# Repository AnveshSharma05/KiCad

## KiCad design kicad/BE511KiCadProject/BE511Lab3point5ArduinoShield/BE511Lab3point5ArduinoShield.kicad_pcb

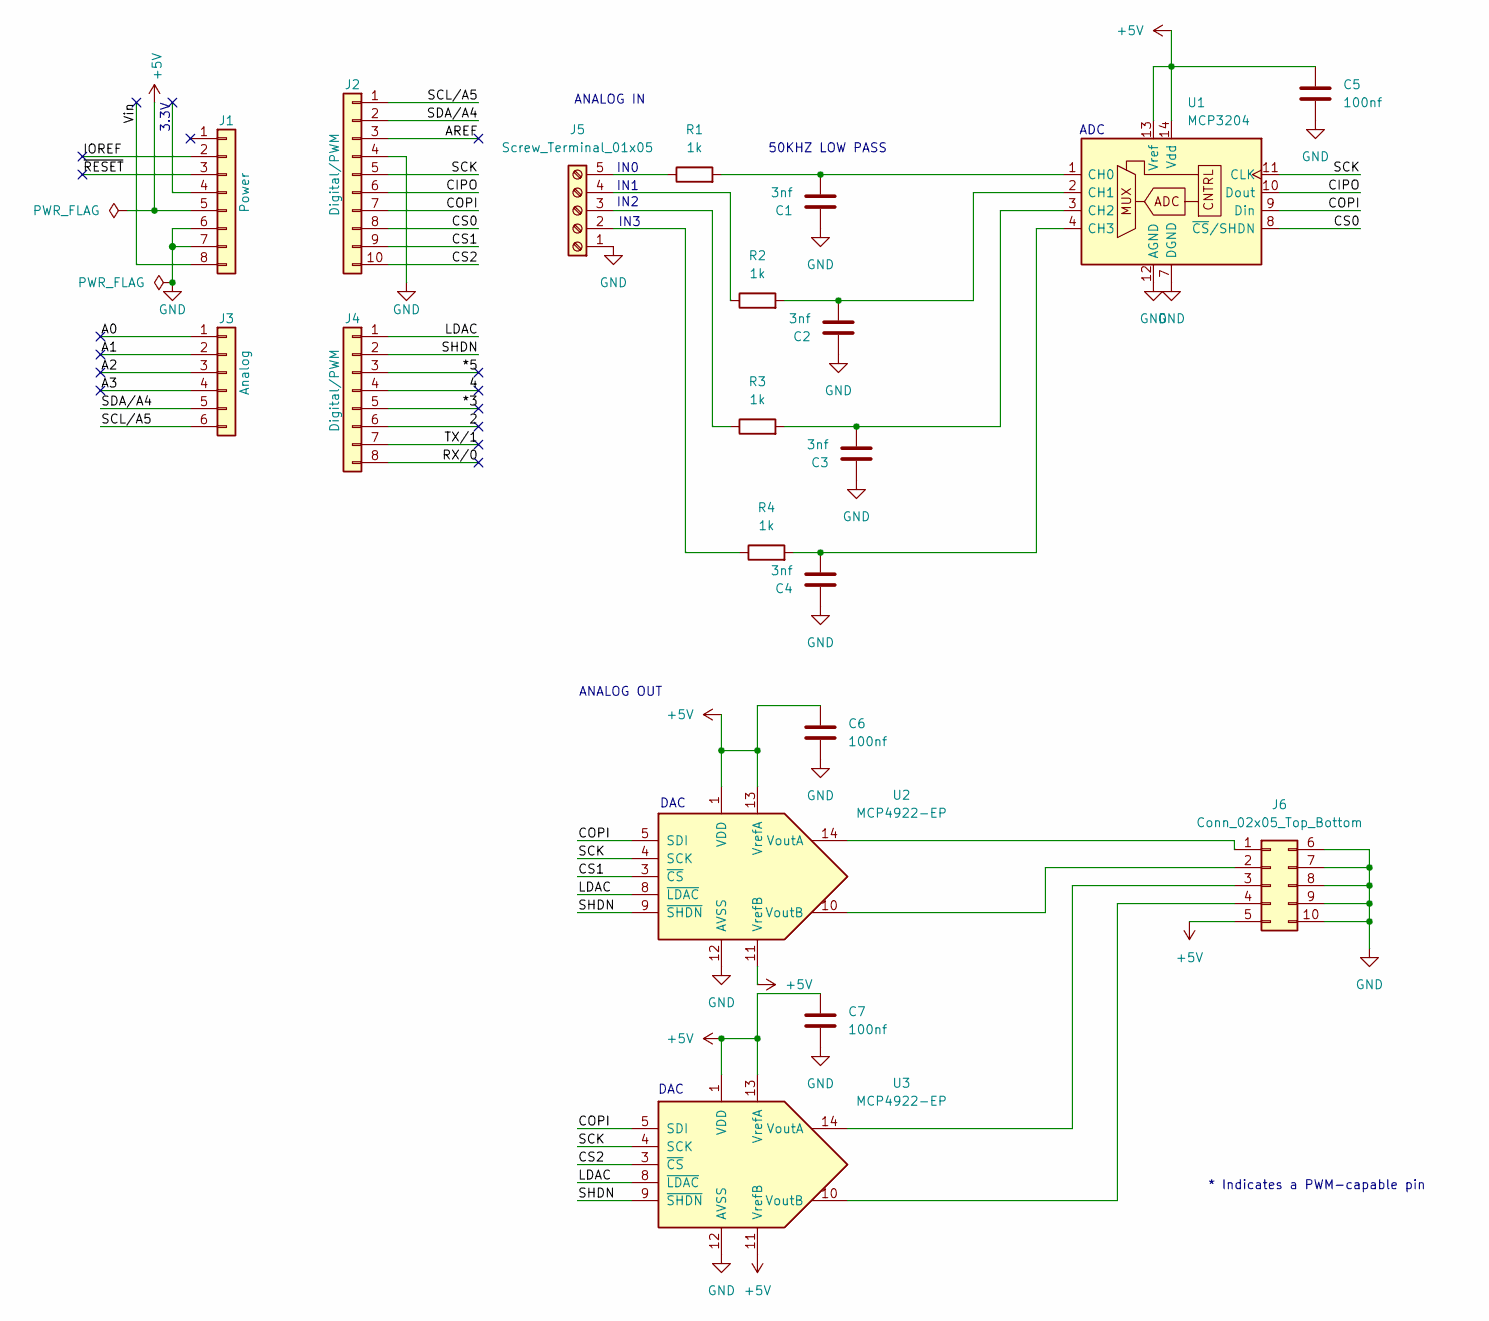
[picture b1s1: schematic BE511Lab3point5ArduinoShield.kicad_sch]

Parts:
C1, C2, C3, C4: 3nf
C5, C6, C7: 100nf
J1: Power; PinSocket_1x08_P2.54mm_Vertical
J2: Digital/PWM; PinSocket_1x10_P2.54mm_Vertical
J3: Analog; PinSocket_1x06_P2.54mm_Vertical
J4: Digital/PWM; PinSocket_1x08_P2.54mm_Vertical
J5: Screw_Terminal_01x05; TerminalBlock_Phoenix_MPT-0,5-5-2.54_1x05_P2.54mm_Horizontal
J6: Conn_02x05_Top_Bottom; PinHeader_2x05_P2.54mm_Vertical
R1, R2, R3, R4: 1k
U1: MCP3204; DIP-14_W7.62mm
U2, U3: MCP4922-EP; DIP-14_W7.62mm

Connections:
+5V: C5.2, C6.2, C7.2, J1.5, J6.5, U1.13 (Vref), U1.14 (Vdd), U2.1 (VDD), U2.11 (VrefB), U2.13 (VrefA), U3.1 (VDD), U3.11 (VrefB), U3.13 (VrefA)
/2: J4.6
/4: J4.4
/*3: J4.5
/*5: J4.3
/A0: J3.1
/A1: J3.2
/A2: J3.3
/A3: J3.4
/AREF: J2.3
/CIPO: J2.6, U1.10 (Dout)
/COPI: J2.7, U1.9 (Din), U2.5 (SDI), U3.5 (SDI)
/CS0: J2.8, U1.8 (~CS/SHDN)
/CS1: J2.9, U2.3 (~CS)
/CS2: J2.10, U3.3 (~CS)
/IOREF: J1.2
/LDAC: J4.1, U2.8 (~LDAC), U3.8 (~LDAC)
/RX/0: J4.8
/SCK: J2.5, U1.11 (CLK), U2.4 (SCK), U3.4 (SCK)
/SCL/A5: J2.1, J3.6
/SDA/A4: J2.2, J3.5
/SHDN: J4.2, U2.9 (~SHDN), U3.9 (~SHDN)
/TX/1: J4.7
/Vin: J1.8
/~RESET: J1.3
GND: C1.1, C2.1, C3.1, C4.1, C5.1, C6.1, C7.1, J1.6, J1.7, J2.4, J5.1, J6.6, J6.7, J6.8, J6.9, J6.10, U1.7 (DGND), U1.12 (AGND), U2.12 (AVSS), U3.12 (AVSS)
unnamed: J5.2, R4.1
unnamed: J5.3, R3.1
unnamed: J5.4, R2.1
unnamed: J5.5, R1.1
unnamed: J6.1, U2.14 (VoutA)
unnamed: J6.2, U2.10 (VoutB)
unnamed: J6.3, U3.14 (VoutA)
unnamed: J6.4, U3.10 (VoutB)
unnamed: C1.2, R1.2, U1.1 (CH0)
unnamed: C2.2, R2.2, U1.2 (CH1)
unnamed: C3.2, R3.2, U1.3 (CH2)
unnamed: C4.2, R4.2, U1.4 (CH3)

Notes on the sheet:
ANALOG IN
DAC
IN2
3.3V
50KHZ LOW PASS
ADC
IN3
IN1
ANALOG OUT
IN0
* Indicates a PWM-capable pin

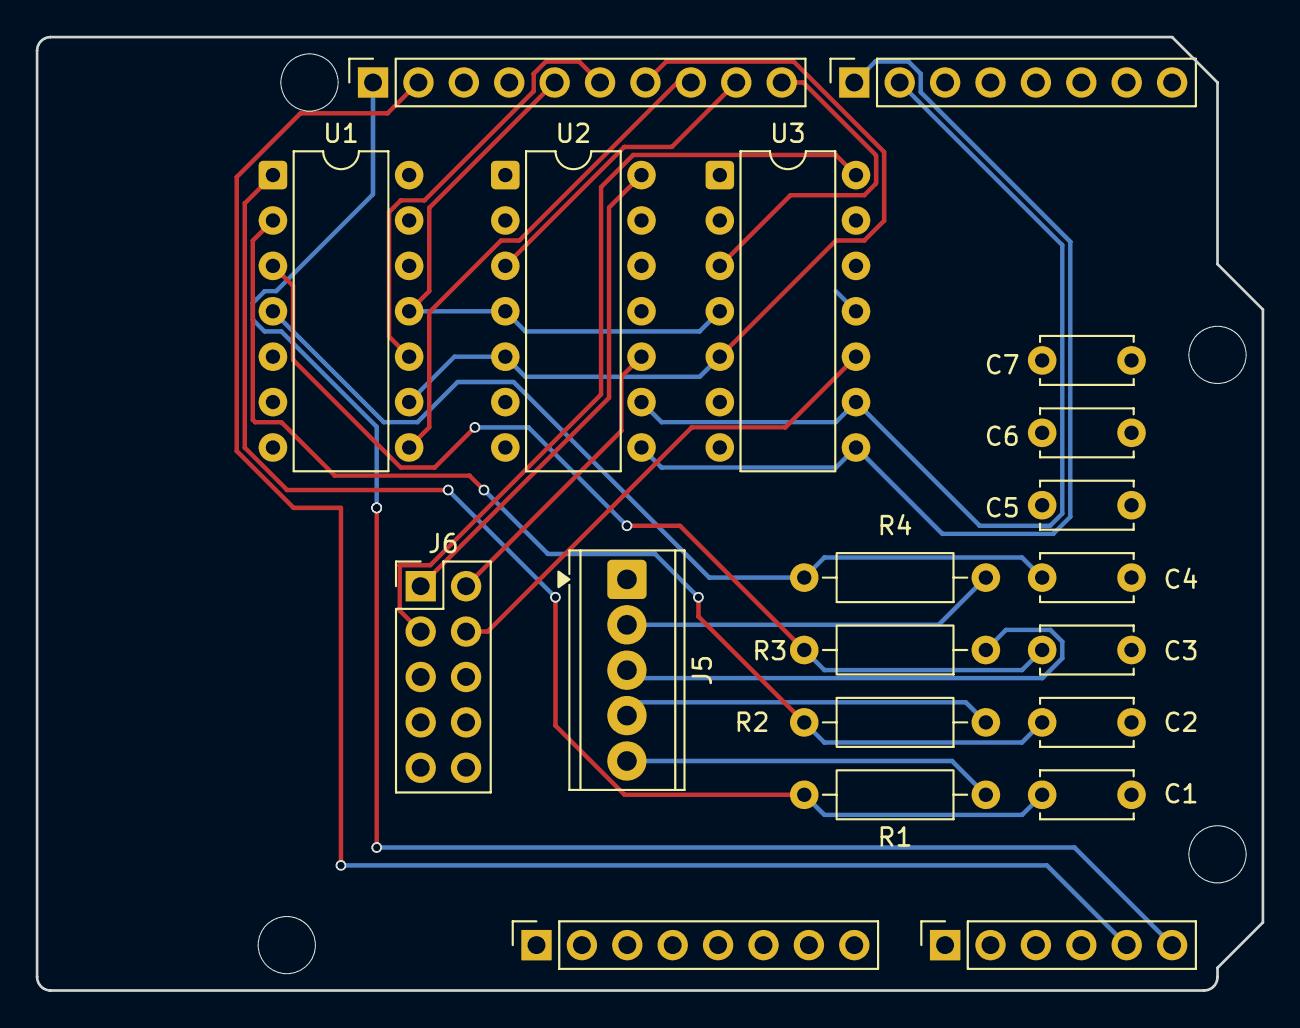
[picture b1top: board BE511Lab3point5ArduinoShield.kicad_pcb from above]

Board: 4 copper layers, 68.6 x 53.3 mm, 24 parts (0 on the bottom side), 24 nets.

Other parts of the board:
MH1, MH2, MH3, MH4: MountingHole_3.2mm
